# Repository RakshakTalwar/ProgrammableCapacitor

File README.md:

Open Source Prototyping Tool. Allows users to rapidly prototype their design by easily allowing the change of a capacitance value in a matter of seconds.

This capable board gives you 4.29 Billion+ capacitance combinations from the range of 0.1pF - 596uF. 

More information can be found at the links below:

[Programamble Capacitor webpage](http://raptorbird.com/capacitor.php)

[Kickstarter Page](https://www.kickstarter.com/projects/raptorbird/programmable-capacitor)

License Information
-------------------
The hardware is released under [Creative Commons Share-alike 3.0](http://creativecommons.org/licenses/by-sa/3.0/).

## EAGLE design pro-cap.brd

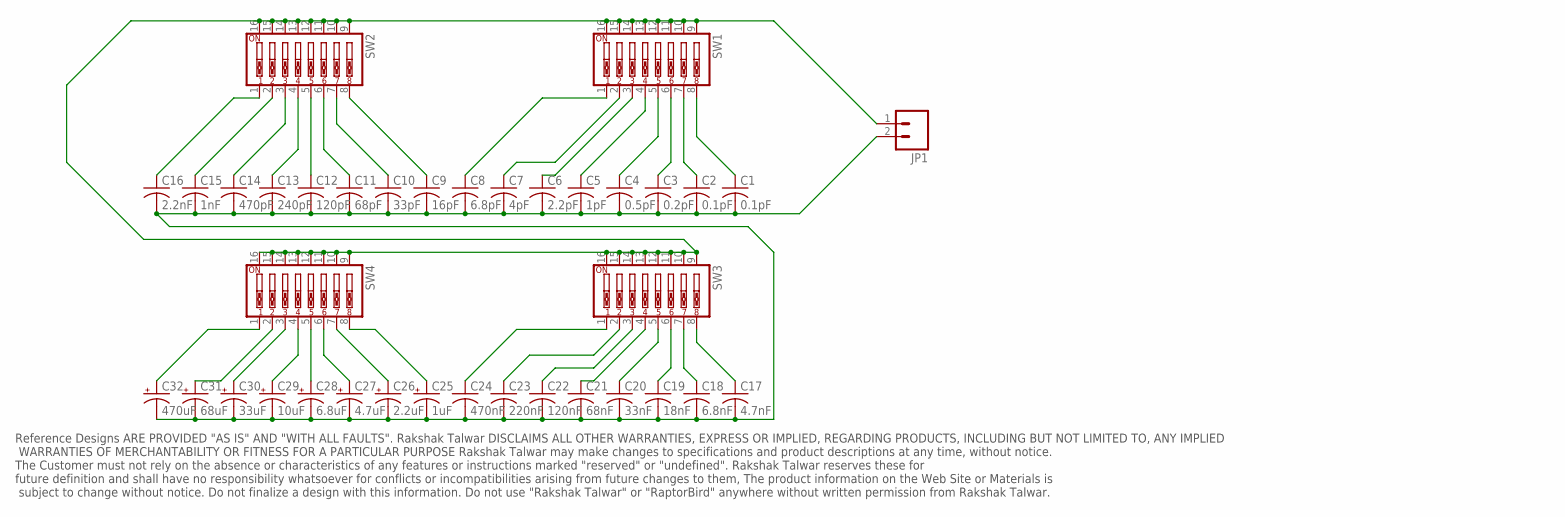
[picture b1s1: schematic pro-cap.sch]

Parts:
C1, C2: 0.1pF; C0603
C3: 0.2pF; C0805
C4: 0.5pF; C0603
C5: 1pF; C0805
C6: 2.2pF; C1206
C7: 4pF; C0603
C8: 6.8pF; C0805
C9: 16pF; C0603
C10: 33pF; C0603
C11: 68pF; C0603
C12: 120pF; C0805
C13: 240pF; C0603
C14: 470pF; C0805
C15: 1nF; C0603
C16: 2.2nF; C0603
C17: 4.7nF; C0603
C18: 6.8nF; C0805
C19: 18nF; C0603
C20: 33nF; C0805
C21: 68nF; C0603
C22: 120nF; C0603
C23: 220nF; C0603
C24: 470nF; C0603
C25: 1uF; PANASONIC_B
C26: 2.2uF; PANASONIC_B
C27: 4.7uF; PANASONIC_B
C28: 6.8uF; E1,8-4
C29: 10uF; E2-5
C30: 33uF; E2-5
C31: 68uF; E2,5-6
C32: 470uF; E5-10,5
JP1: M023.5MM; SCREWTERMINAL-3.5MM-2
SW1, SW2, SW3, SW4: SW_DIP-8; EDG-08

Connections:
unnamed: C1.1, SW1.8
unnamed: C2.1, SW1.7
unnamed: C3.1, SW1.6
unnamed: C4.1, SW1.5
unnamed: C5.1, SW1.4
unnamed: C6.1, SW1.3
unnamed: C7.1, SW1.2
unnamed: C8.1, SW1.1
unnamed: C9.1, SW2.8
unnamed: C10.1, SW2.7
unnamed: C11.1, SW2.6
unnamed: C12.1, SW2.5
unnamed: C13.1, SW2.4
unnamed: C14.1, SW2.3
unnamed: C15.1, SW2.2
unnamed: C16.1, SW2.1
unnamed: C17.1, SW3.8
unnamed: C18.1, SW3.7
unnamed: C19.1, SW3.6
unnamed: C20.1, SW3.5
unnamed: C21.1, SW3.4
unnamed: C22.1, SW3.3
unnamed: C23.1, SW3.2
unnamed: C24.1, SW3.1
unnamed: C25.+, SW4.8
unnamed: C26.+, SW4.7
unnamed: C27.+, SW4.6
unnamed: C28.+, SW4.5
unnamed: C29.+, SW4.4
unnamed: C30.+, SW4.3
unnamed: C31.+, SW4.2
unnamed: C32.+, SW4.1
unnamed: JP1.1, SW1.9, SW1.10, SW1.11, SW1.12, SW1.13, SW1.14, SW1.15, SW1.16, SW2.9, SW2.10, SW2.11, SW2.12, SW2.13, SW2.14, SW2.15, SW2.16, SW3.9, SW3.10, SW3.11, SW3.12, SW3.13, SW3.14, SW3.15, SW3.16, SW4.9, SW4.10, SW4.11, SW4.12, SW4.13, SW4.14, SW4.15, SW4.16
unnamed: C1.2, C2.2, C3.2, C4.2, C5.2, C6.2, C7.2, C8.2, C9.2, C10.2, C11.2, C12.2, C13.2, C14.2, C15.2, C16.2, C17.2, C18.2, C19.2, C20.2, C21.2, C22.2, C23.2, C24.2, C25.-, C26.-, C27.-, C28.-, C29.-, C30.-, C31.-, C32.-, JP1.2

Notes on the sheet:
Reference Designs ARE PROVIDED "AS IS" AND "WITH ALL FAULTS". Rakshak Talwar DISCLAIMS ALL OTHER WARRANTIES, EXPRESS OR IMPLIED, REGARDING PRODUCTS, INCLUDING BUT NOT LIMITED TO, ANY IMPLIED WARRANTIES OF MERCHANTABILITY OR FITNESS FOR A PARTICULAR PURPOSE Rakshak Talwar may make changes to specifi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

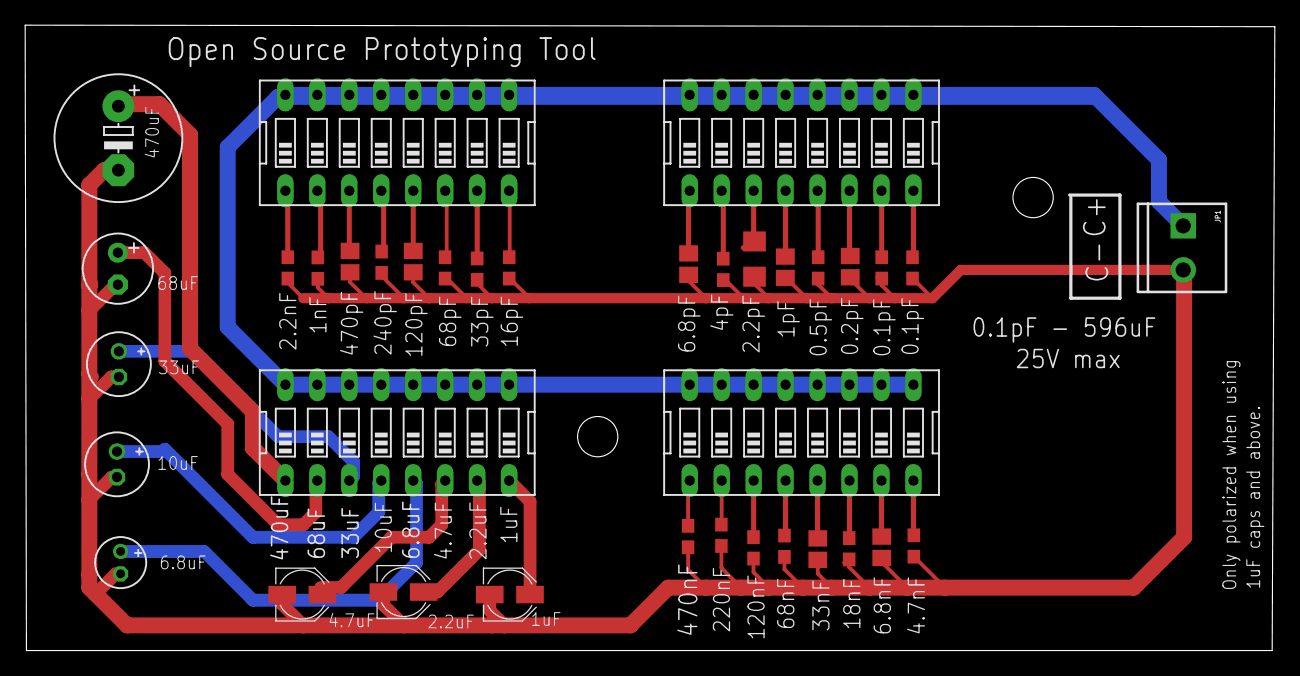
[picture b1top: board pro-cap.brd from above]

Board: 2 copper layers, 99.3 x 49.7 mm, 37 parts (0 on the bottom side), 34 nets.

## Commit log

2014-02-09 EAGLE files
    Includes board and schematic files.

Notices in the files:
pro-cap.brd:
Creative Commons BY-SA 3.0
parts and their libraries:
SparkFun-Connectors: Licensing: CC v3.0 Share-Alike You are welcome to use this library for commercial purposes.
